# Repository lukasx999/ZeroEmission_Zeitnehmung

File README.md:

# ZeroEmission_Zeitnehmung

Hier finden Sie sowohl den Quellcode als auch eine ausführliche Anleitung für unser ZeroEmission Zeitmessungssystem. Das System wurde entwickelt, um präzise Rundenzeiten während Zero-Emission-Challenges zu erfassen und bietet eine elegante Lösung durch den Einsatz fortschrittlicher Lichtschranken-Technologie. Die umfassende und ausführliche Anleitung ist im PDF-Dokument '00_ZeroEmission_Zeitnehmung_v1.3.pdf' verfügbar.

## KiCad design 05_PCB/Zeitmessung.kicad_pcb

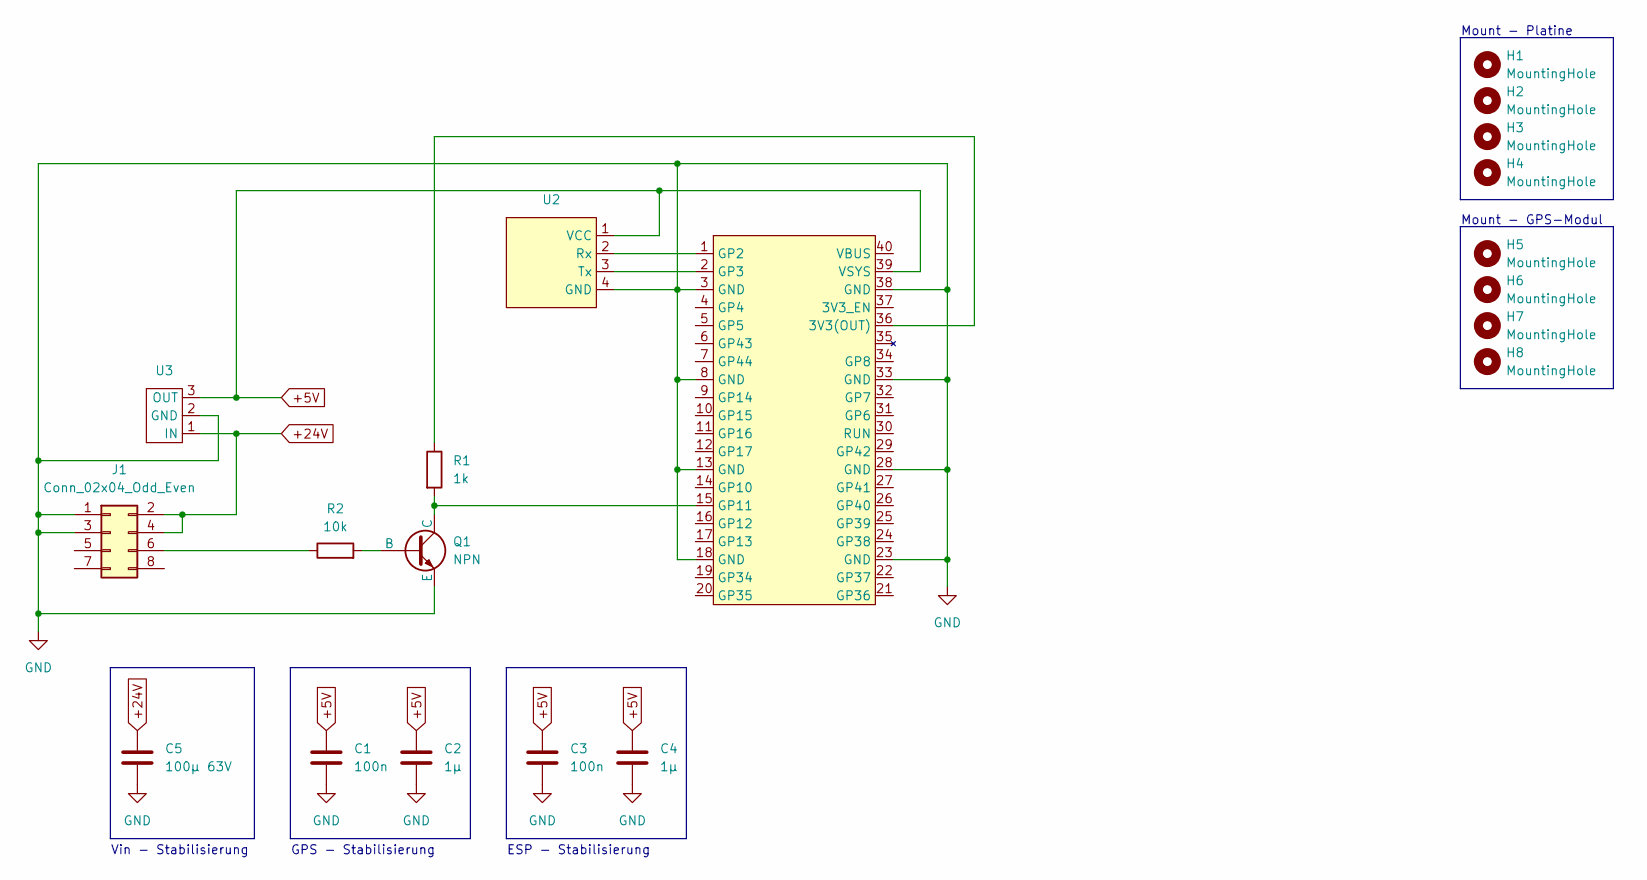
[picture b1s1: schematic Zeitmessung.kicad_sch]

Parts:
C1, C3: 100n; C_0805_2012Metric
C2, C4: 1µ; C_0805_2012Metric
C5: 100µ 63V; C_0805_2012Metric
H1, H2, H3, H4, H5, H6, H7, H8: MountingHole; MountingHole_2.1mm
J1: Conn_02x04_Odd_Even; Samtec_HLE-104-02-xx-DV-TE_2x04_P2.54mm_Horizontal
Q1: NPN; TO-92
R1: 1k; R_Axial_DIN0411_L9.9mm_D3.6mm_P15.24mm_Horizontal
R2: 10k; R_Axial_DIN0411_L9.9mm_D3.6mm_P15.24mm_Horizontal
U1: ESP32-S2-LCD
U2: GPS
U3: DC-DC-Wandler

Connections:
+5V: C1.1, C2.1, C3.1, C4.1, U1.39 (VSYS), U2.1 (VCC), U3.3 (OUT)
+24V: C5.1, J1.2, J1.4, U3.1 (IN)
GND: C1.2, C2.2, C3.2, C4.2, C5.2, J1.1, J1.3, Q1.3 (E), U1.3 (GND), U1.8 (GND), U1.13 (GND), U1.18 (GND), U1.23 (GND), U1.28 (GND), U1.33 (GND), U1.38 (GND), U2.4 (GND), U3.2 (GND)
unnamed: J1.6, R2.1
unnamed: Q1.2 (B), R2.2
unnamed: Q1.1 (C), R1.2, U1.15 (GP11)
unnamed: R1.1, U1.36 (3V3(OUT))
unnamed: U1.1 (GP2), U2.2 (Rx)
unnamed: U1.2 (GP3), U2.3 (Tx)

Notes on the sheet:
Mount - Platine
Mount - GPS-Modul
ESP - Stabilisierung
Vin - Stabilisierung
GPS - Stabilisierung

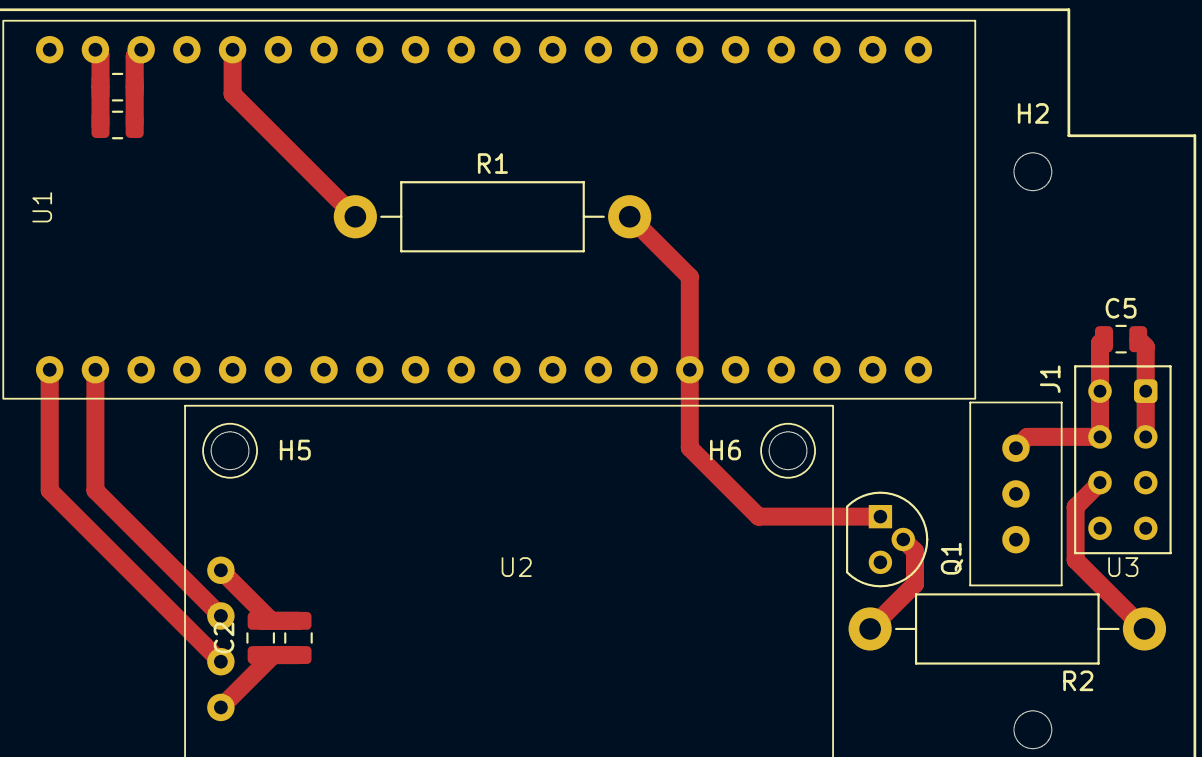
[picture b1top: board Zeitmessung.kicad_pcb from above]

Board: 4 copper layers, 20 parts (0 on the bottom side), 9 nets.

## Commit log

2023-12-22 upload of all the programms
2023-12-26 Flask app support for Apache2
2023-12-26 added folder
2024-01-09 added documentation
2024-01-09 small changes
2024-01-10 updated documenation
2024-02-09 added build flags for TFT display configuration
2024-02-09 updated tft config
2024-02-12 updated doku
2024-04-10 added PCB and casing
2024-04-10 updated casing
2024-04-10 updated documentation
2024-10-10 forked!
2024-10-15 auto attemptnr, config.json for pre setup, update DB models, include energy not finished
2024-10-19 points working, pdf generation - working version
2024-10-23 slalom start and end added, clear radios, warning messges - zec2024 version
2024-10-24 team time pdf export added
2024-10-24 LichtschrankenStation Version ZEC 24, no GPS, NTP used
